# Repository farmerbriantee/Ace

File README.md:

# AgOpenGPS  ****  Ace

Ace is a new way to run AOG where the modules are small, and everything is on the udp network.

This is a development Repo and changes often. 

*** Important ****

If you distribute copies of such a program, whether
gratis or for a fee, you must pass on to the recipients the same
freedoms that you received.  You must make sure that they, too, receive
or can get the source code.  And you must show them these terms so they
know their rights as Outlined in the GPLv3 License.

THIS SOFTWARE IS PROVIDED BY THE COPYRIGHT HOLDERS AND CONTRIBUTORS "AS IS" AND ANY EXPRESS OR IMPLIED WARRANTIES, INCLUDING, BUT NOT LIMITED TO, THE IMPLIED WARRANTIES OF MERCHANTABILITY AND FITNESS FOR A PARTICULAR PURPOSE ARE DISCLAIMED.
IN NO EVENT SHALL <COPYRIGHT HOLDER> BE LIABLE FOR ANY DIRECT, INDIRECT, INCIDENTAL, SPECIAL, EXEMPLARY, OR CONSEQUENTIAL DAMAGES (INCLUDING, BUT NOT LIMITED TO, PROCUREMENT OF SUBSTITUTE GOODS OR SERVICES;
LOSS OF USE, DATA, OR PROFITS; OR BUSINESS INTERRUPTION) HOWEVER CAUSED AND ON ANY THEORY OF LIABILITY, WHETHER IN CONTRACT, STRICT LIABILITY, OR TORT (INCLUDING NEGLIGENCE OR OTHERWISE) ARISING IN ANY WAY OUT OF THE USE OF THIS SOFTWARE, EVEN IF ADVISED OF THE POSSIBILITY OF SUCH DAMAGE.

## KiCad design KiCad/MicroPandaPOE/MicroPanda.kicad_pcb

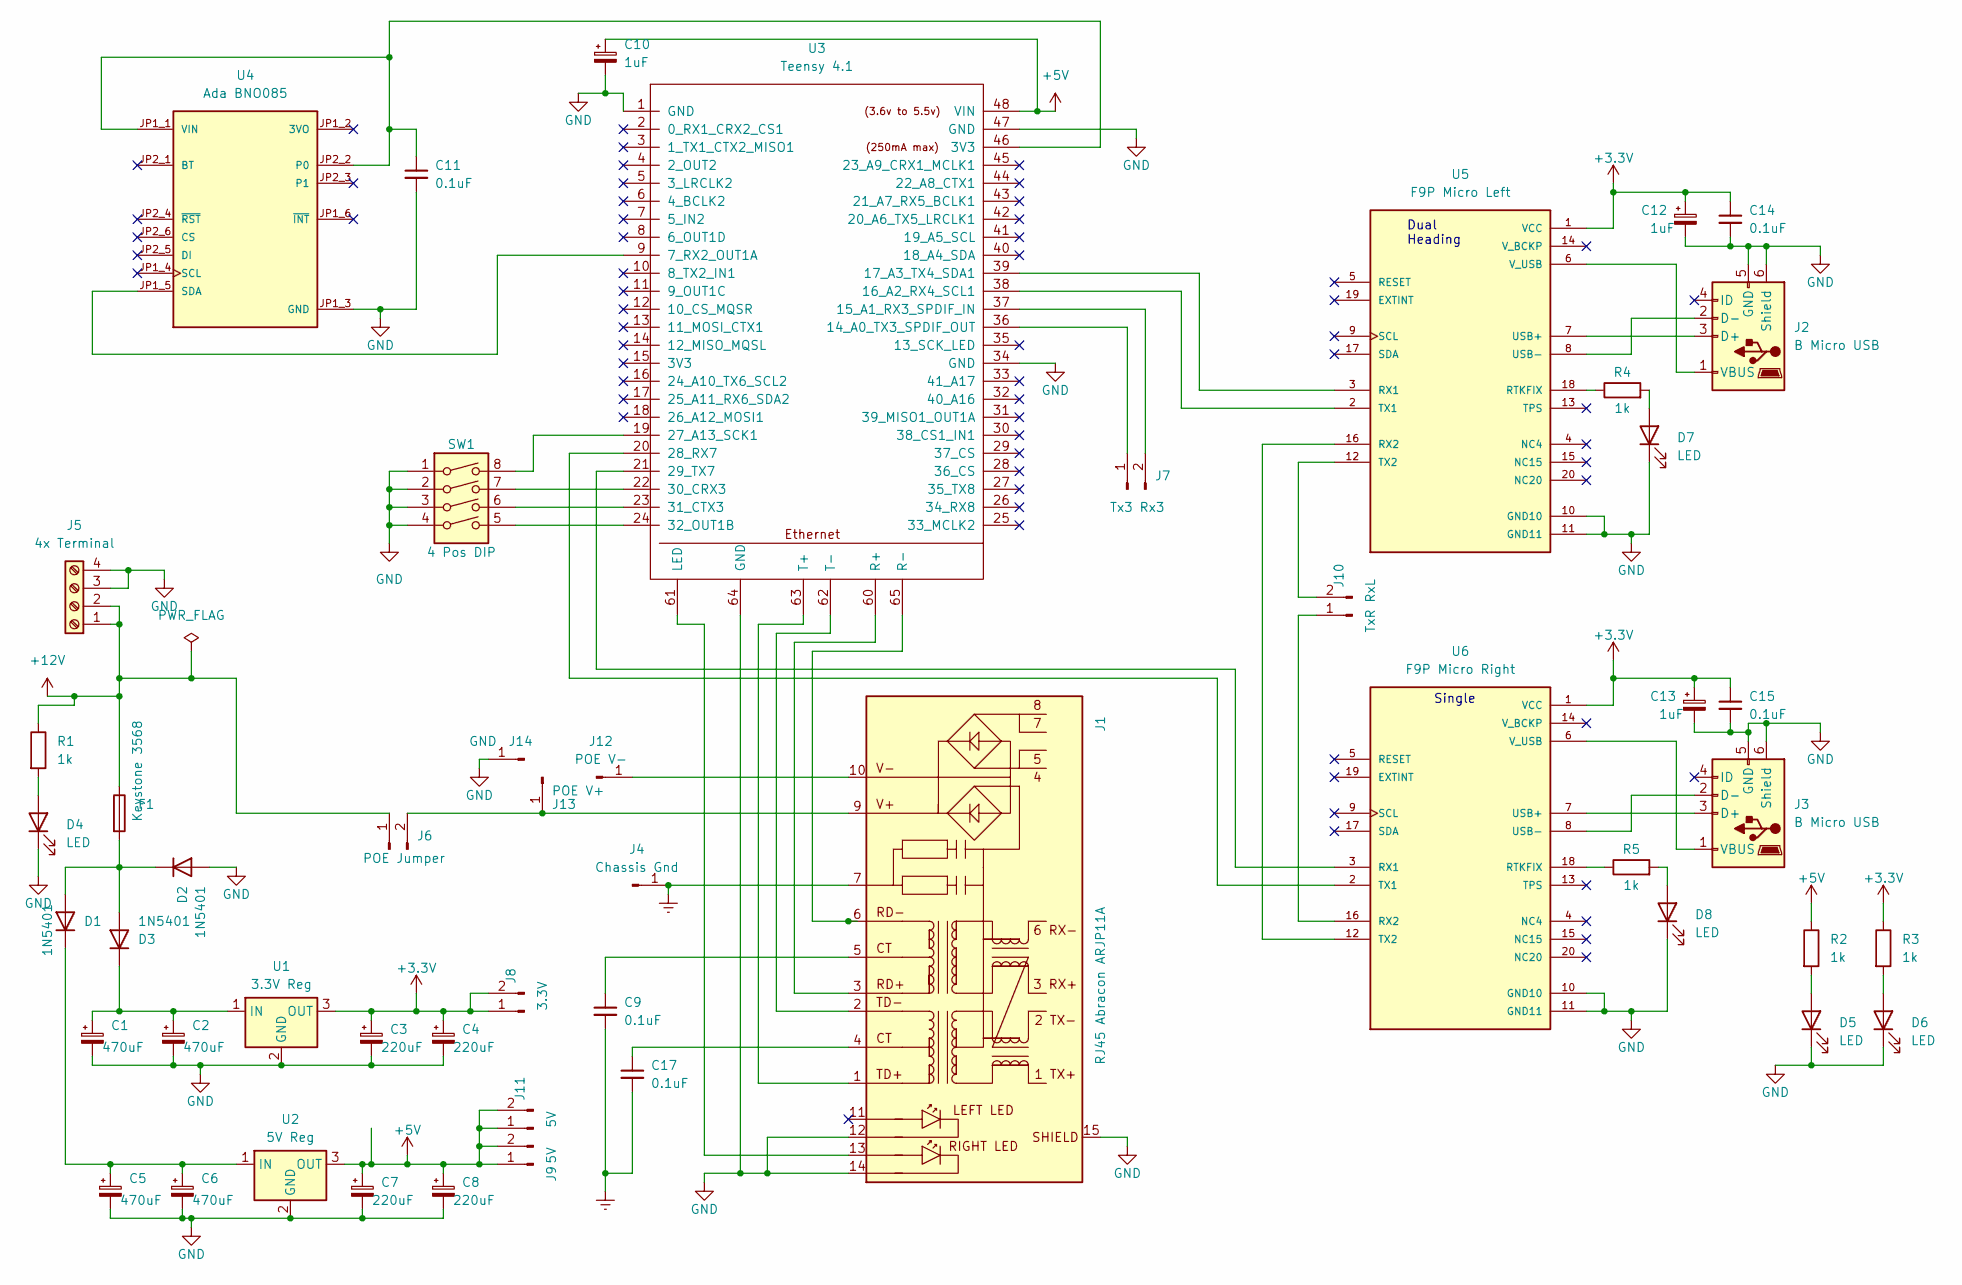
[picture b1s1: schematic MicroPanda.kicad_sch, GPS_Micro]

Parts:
C1, C2, C5, C6: 470uF; CP_Radial_D8.0mm_P5.00mm
C3, C4, C7, C8: 220uF; CP_Radial_D8.0mm_P3.50mm
C9, C11, C14, C15, C17: 0.1uF; C_Disc_D7.0mm_W2.5mm_P5.00mm
C10, C12, C13: 1uF; CP_Radial_D6.3mm_P2.50mm
D1, D2, D3: 1N5401; D_DO-201AD_P15.24mm_Horizontal
D4, D5, D6, D7, D8: LED; LED_D2.0mm_W4.0mm_H2.8mm_FlatTop
F1: Keystone 3568; Fuseholder_Blade_Mini_Keystone_3568
J1: RJ45 Abracon ARJP11A; RJ45_Abracon_ARJP11A-MA_Horizontal
J2, J3: B Micro USB; USB_Mini_B_AdamTech_musb_b5_s_vt_02_TH
J4: Chassis Gnd; Pin_D1.3mm_L11.0mm_LooseFit
J5: 4x Terminal; TerminalBlock_Phoenix_MKDS-1,5-4-5.08_1x04_P5.08mm_Horizont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
J6: POE Jumper; PinSocket_1x02_P2.54mm_Vertical
J7: Tx3 Rx3; PinSocket_1x02_P2.54mm_Vertical
J8: 3.3V; PinSocket_1x02_P2.54mm_Vertical
J9, J11: 5V; PinSocket_1x02_P2.54mm_Vertical
J10: TxR RxL; PinSocket_1x02_P2.54mm_Vertical
J12: POE V-; Pin_D1.3mm_L11.0mm_LooseFit
J13: POE V+; Pin_D1.3mm_L11.0mm_LooseFit
J14: GND; Pin_D1.3mm_L11.0mm_LooseFit
R1, R2, R3: 1k; R_Axial_DIN0207_L6.3mm_D2.5mm_P10.16mm_Horizontal
R4, R5: 1k; R_Axial_DIN0204_L3.6mm_D1.6mm_P2.54mm_Vertical
SW1: 4 Pos DIP; SW_DIP_SPSTx04_Slide_9.78x12.34mm_W7.62mm_P2.54mm
U1: 3.3V Reg; Converter_DCDC_Murata_OKI-78SR_Vertical
U2: 5V Reg; Converter_DCDC_Murata_OKI-78SR_Vertical
U3: Teensy 4.1; Teensy41_BGT
U4: Ada BNO085; BNO085_Adafruit_4754; PARTREV 2021-03-16
U5: F9P Micro Left; MODULE_AS-RTK2B-MICRO-F9P-L1L2SMATH-00; PARTREV N/A
U6: F9P Micro Right; MODULE_AS-RTK2B-MICRO-F9P-L1L2SMATH-00; PARTREV N/A

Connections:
+3.3V: C3.1, C4.1, C12.1, C13.1, C14.1, C15.1, J8.1, J8.2, R3.1, U1.3 (OUT), U5.1 (VCC), U6.1 (VCC)
+5V: C7.1, C8.1, C10.1, J9.1, J9.2, J11.1, J11.2, R2.1, U2.3 (OUT), U3.48 (VIN)
+12V: F1.1, J5.1, J5.2, J6.1, R1.1
Earth: C9.2, C17.2, J1.7, J4.1
GND: C1.2, C2.2, C3.2, C4.2, C5.2, C6.2, C7.2, C8.2, C10.2, C11.2, C12.2, C13.2, C14.2, C15.2, D2.2 (A), D4.1 (K), D5.1 (K), D6.1 (K), D7.1 (K), D8.1 (K), J1.12 (LLED-), J1.14 (RLED-), J1.15 (SHIELD), J2.5 (GND), J2.6 (Shield), J3.5 (GND), J3.6 (Shield), J5.3, J5.4, J14.1, SW1.1, SW1.2, SW1.3, SW1.4, U1.2 (GND), U2.2 (GND), U3.1 (GND), U3.34 (GND), U3.47 (GND), U3.64 (GND), U4.JP1_3 (GND), U5.10 (GND10), U5.11 (GND11), U6.10 (GND10), U6.11 (GND11)
unnamed: C1.1, C2.1, D3.1 (K), U1.1 (IN)
unnamed: C5.1, C6.1, D1.1 (K), U2.1 (IN)
unnamed: C9.1, J1.5 (CT)
unnamed: C11.1, U3.46 (3V3), U4.JP1_1 (VIN), U4.JP2_2 (P0)
unnamed: C17.1, J1.4 (CT)
unnamed: D1.2 (A), D2.1 (K), D3.2 (A), F1.2
unnamed: D4.2 (A), R1.2
unnamed: D5.2 (A), R2.2
unnamed: D6.2 (A), R3.2
unnamed: D7.2 (A), R4.2
unnamed: D8.2 (A), R5.2
unnamed: J1.1 (TD+), U3.63 (T+)
unnamed: J1.2 (TD-), U3.62 (T-)
unnamed: J1.3 (RD+), U3.60 (R+)
unnamed: J1.6 (RD-), U3.65 (R-)
unnamed: J1.9 (V+), J6.2, J13.1
unnamed: J1.10 (V-), J12.1
unnamed: J1.13 (RLED+), U3.61 (LED)
unnamed: J2.1 (VBUS), U5.6 (V_USB)
unnamed: J2.2 (D-), U5.8 (USB-)
unnamed: J2.3 (D+), U5.7 (USB+)
unnamed: J3.1 (VBUS), U6.6 (V_USB)
unnamed: J3.2 (D-), U6.8 (USB-)
unnamed: J3.3 (D+), U6.7 (USB+)
unnamed: J7.1, U3.36 (14_A0_TX3_SPDIF_OUT)
unnamed: J7.2, U3.37 (15_A1_RX3_SPDIF_IN)
unnamed: J10.1, U6.16 (RX2)
unnamed: J10.2, U5.12 (TX2)
unnamed: R4.1, U5.18 (RTKFIX)
unnamed: R5.1, U6.18 (RTKFIX)
unnamed: SW1.5, U3.24 (32_OUT1B)
unnamed: SW1.6, U3.23 (31_CTX3)
unnamed: SW1.7, U3.22 (30_CRX3)
unnamed: SW1.8, U3.19 (27_A13_SCK1)
unnamed: U3.9 (7_RX2_OUT1A), U4.JP1_5 (SDA)
unnamed: U3.20 (28_RX7), U6.2 (TX1)
unnamed: U3.21 (29_TX7), U6.3 (RX1)
unnamed: U3.38 (16_A2_RX4_SCL1), U5.2 (TX1)
unnamed: U3.39 (17_A3_TX4_SDA1), U5.3 (RX1)
unnamed: U5.16 (RX2), U6.12 (TX2)

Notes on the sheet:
Dual Heading
Single

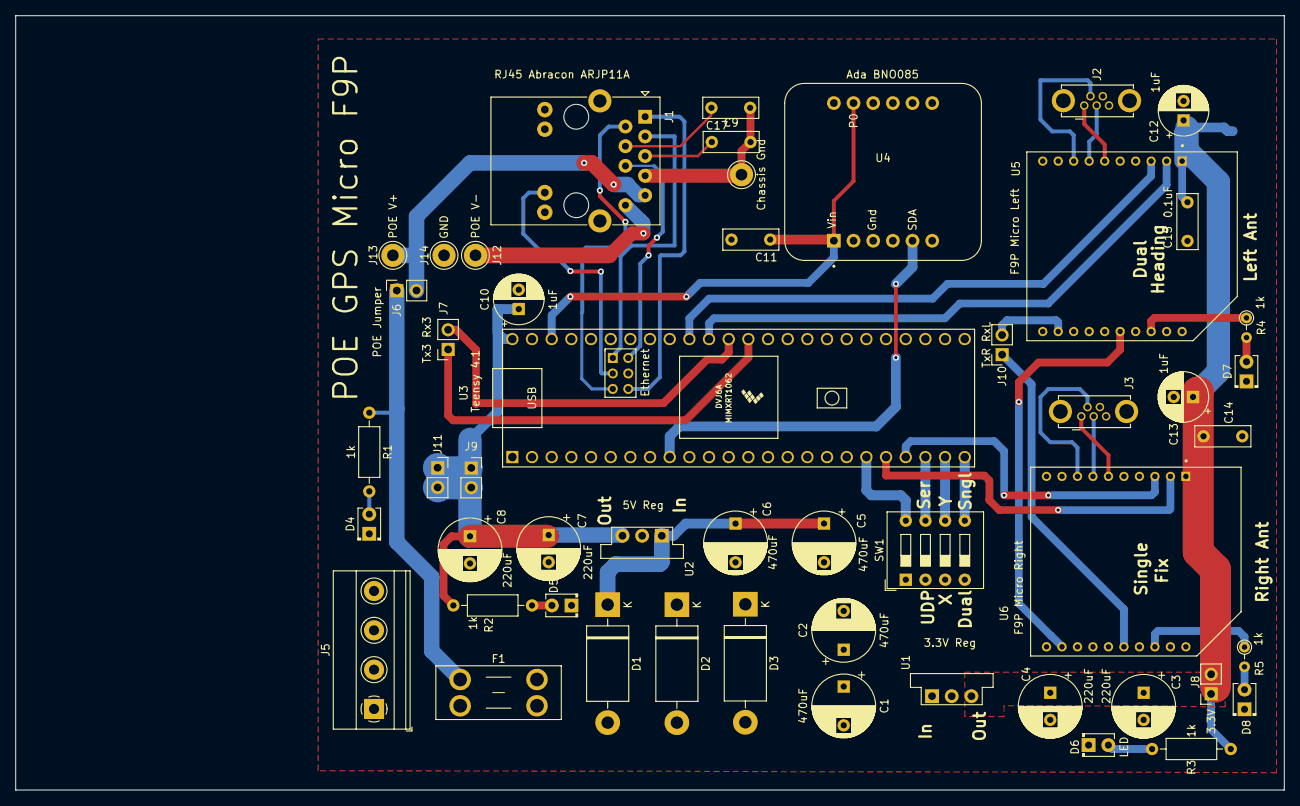
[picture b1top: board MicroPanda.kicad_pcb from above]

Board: 2 copper layers, 163.8 x 100.0 mm, 51 parts (0 on the bottom side), 45 nets.

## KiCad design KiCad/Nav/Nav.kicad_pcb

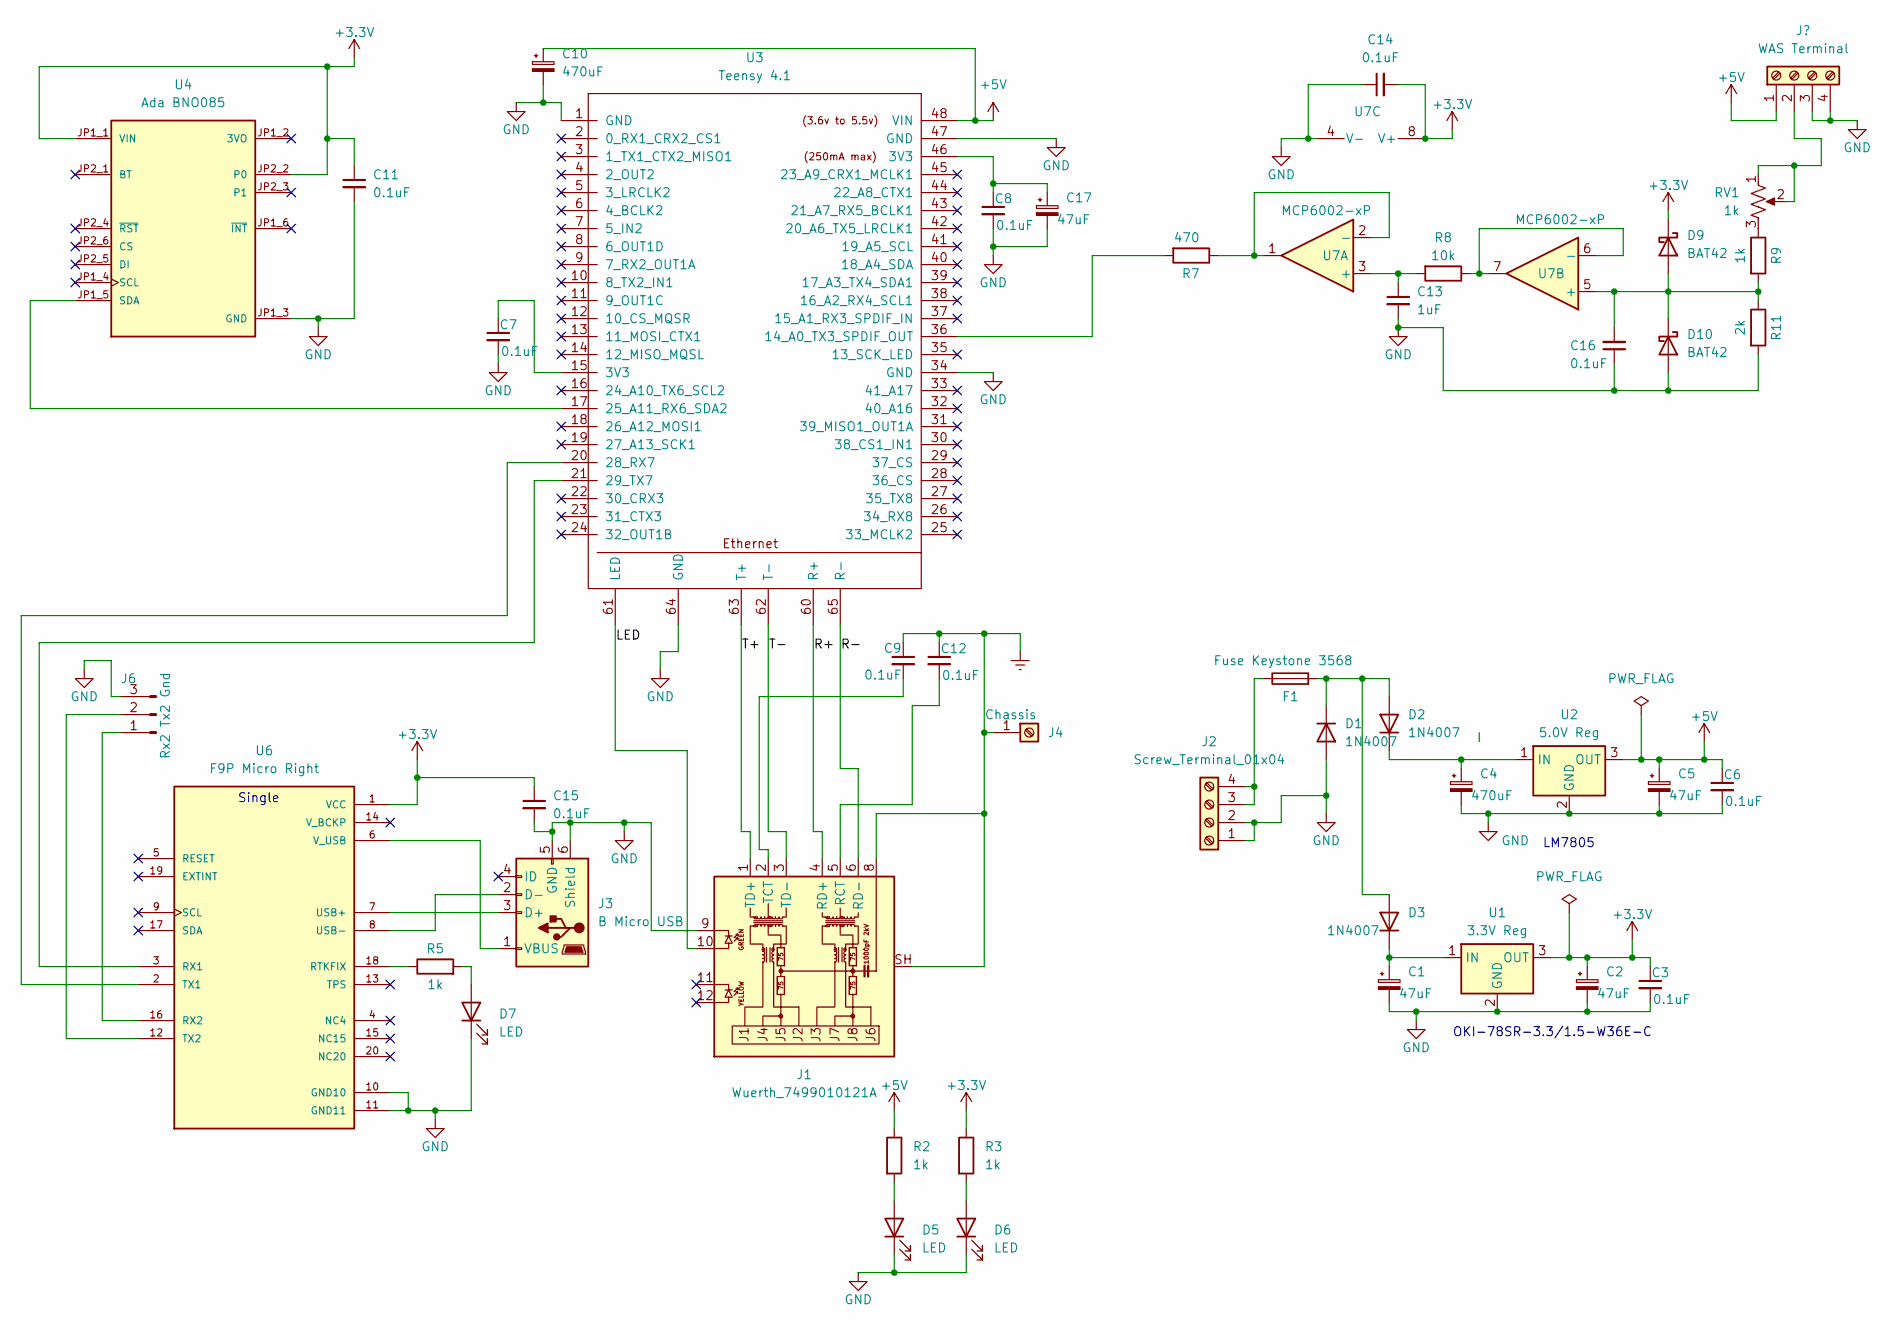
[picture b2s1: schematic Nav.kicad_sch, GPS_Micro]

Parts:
C1, C2, C5, C17: 47uF; CP_Radial_D5.0mm_P2.50mm
C3, C6, C7, C8, C9, C11, C12, C14, C15, C16: 0.1uF; C_Disc_D7.0mm_W2.5mm_P5.00mm
C4, C10: 470uF; CP_Radial_D10.0mm_P5.00mm
C13: 1uF; C_Disc_D7.0mm_W2.5mm_P5.00mm
D1, D2, D3: 1N4007; D_DO-41_SOD81_P10.16mm_Horizontal
D5, D6, D7: LED; LED_D2.0mm_W4.0mm_H2.8mm_FlatTop
D9, D10: BAT42; D_DO-35_SOD27_P7.62mm_Horizontal
F1: Fuse Keystone 3568; Fuseholder_Blade_Mini_Keystone_3568
J1: Wuerth_7499010121A; RJ45_Wuerth_7499010121A_Horizontal
J2: Screw_Terminal_01x04; TerminalBlock_TE_282834-4_1x04_P2.54mm_Horizontal
J3: B Micro USB; USB_Mini_B_AdamTech_musb_b5_s_vt_02_TH
J4: Chassis; Pin_D1.3mm_L11.3mm_W2.8mm_Flat
J6: Rx2 Tx2 Gnd; PinHeader_1x03_P2.54mm_Vertical
R2, R3, R5, R9: 1k; R_Axial_DIN0207_L6.3mm_D2.5mm_P10.16mm_Horizontal
R7: 470; R_Axial_DIN0207_L6.3mm_D2.5mm_P10.16mm_Horizontal
R8: 10k; R_Axial_DIN0207_L6.3mm_D2.5mm_P10.16mm_Horizontal
R11: 2k; R_Axial_DIN0207_L6.3mm_D2.5mm_P10.16mm_Horizontal
RV1: 1k; Potentiometer_Bourns_3296Y_Vertical
U1: 3.3V Reg; Converter_DCDC_Murata_OKI-78SR_Vertical
U2: 5.0V Reg; Converter_DCDC_Murata_OKI-78SR_Vertical
U3: Teensy 4.1; Teensy41_BGT
U4: Ada BNO085; BNO085_Adafruit_4754; PARTREV 2021-03-16
U6: F9P Micro Right; MODULE_AS-RTK2B-MICRO-F9P-L1L2SMATH-00; PARTREV N/A
U7: MCP6002-xP; DIP-8_W7.62mm

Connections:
+3.3V: C2.1, C3.1, C11.1, C14.2, C15.1, D9.1 (K), R3.1, U1.3 (OUT), U4.JP1_1 (VIN), U4.JP2_2 (P0), U6.1 (VCC), U7.8 (V+)
+5V: C5.1, C6.1, C10.1, R2.1, U2.3 (OUT), U3.48 (VIN); also elsewhere on the board
/LED: J1.10, U3.61 (LED)
/R+: J1.4 (RD+), U3.60 (R+)
/R-: J1.6 (RD-), U3.65 (R-)
/T+: J1.1 (TD+), U3.63 (T+)
/T-: J1.3 (TD-), U3.62 (T-)
Earth: C9.1, C12.1, J1.8, J1.SH, J4.1
GND: C1.2, C2.2, C3.2, C4.2, C5.2, C6.2, C7.2, C8.2, C10.2, C11.2, C13.2, C14.1, C15.2, C16.1, C17.2, D1.2 (A), D5.1 (K), D6.1 (K), D7.1 (K), D10.2 (A), J1.9, J2.1, J2.2, J3.5 (GND), J3.6 (Shield), J6.3, R11.2, U1.2 (GND), U2.2 (GND), U3.1 (GND), U3.34 (GND), U3.47 (GND), U3.64 (GND), U4.JP1_3 (GND), U6.10 (GND10), U6.11 (GND11), U7.4 (V-); also elsewhere on the board
unnamed: C1.1, D3.1 (K), U1.1 (IN)
unnamed: C4.1, D2.1 (K), U2.1 (IN)
unnamed: C7.1, U3.15 (3V3)
unnamed: C9.2, J1.2 (TCT)
unnamed: C12.2, J1.5 (RCT)
unnamed: C13.1, R8.2, U7.3 (+)
unnamed: C16.2, D9.2 (A), D10.1 (K), R9.2, R11.1, U7.5 (+)
unnamed: C8.1, C17.1, U3.46 (3V3)
unnamed: D1.1 (K), D2.2 (A), D3.2 (A), F1.2
unnamed: D5.2 (A), R2.2
unnamed: D6.2 (A), R3.2
unnamed: D7.2 (A), R5.2
unnamed: F1.1, J2.3, J2.4
unnamed: J3.1 (VBUS), U6.6 (V_USB)
unnamed: J3.2 (D-), U6.8 (USB-)
unnamed: J3.3 (D+), U6.7 (USB+)
unnamed 25: RV1.1, RV1.2; also elsewhere on the board
unnamed: J6.1, U6.16 (RX2)
unnamed: J6.2, U6.12 (TX2)
unnamed: R7.1, U7.1, U7.2 (-)
unnamed: R7.2, U3.36 (14_A0_TX3_SPDIF_OUT)
unnamed: R8.1, U7.6 (-), U7.7
unnamed: R9.1, RV1.3
unnamed: U3.17 (25_A11_RX6_SDA2), U4.JP1_5 (SDA)
unnamed: U3.20 (28_RX7), U6.2 (TX1)
unnamed: U3.21 (29_TX7), U6.3 (RX1)
unnamed: R5.1, U6.18 (RTKFIX)

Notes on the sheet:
OKI-78SR-3.3/1.5-W36E-C
LM7805
Single

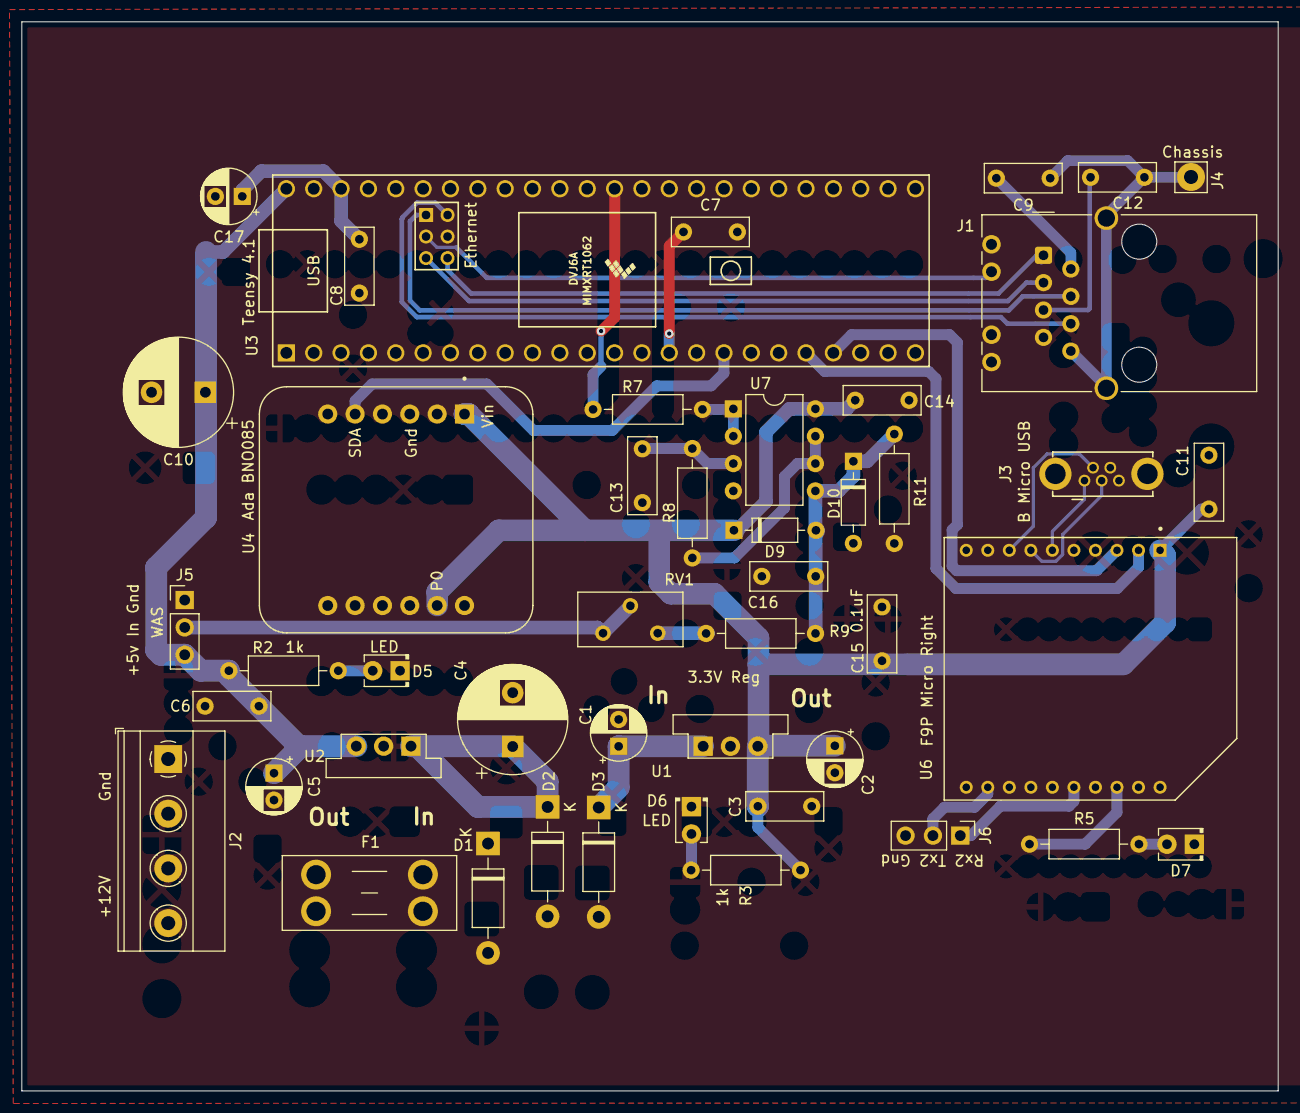
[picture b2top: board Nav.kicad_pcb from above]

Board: 2 copper layers, 116.7 x 99.3 mm, 46 parts (0 on the bottom side), 36 nets.

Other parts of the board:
J5: +5v In Gnd; PinHeader_1x03_P2.54mm_Vertical

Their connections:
+5V: J5.3; also elsewhere on the board
GND: J5.1; also elsewhere on the board
unnamed 25: J5.2; also elsewhere on the board

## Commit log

2023-02-28 initial push
2023-02-28 Fix double hardware
2023-02-28 build solutions
2023-03-01 Entered one comment lets see if this breaks github
2023-03-01 Revert "Entered one comment lets see if this breaks github"
    This reverts commit 4174c9bc2cd81f1f32c803d15affabef2187f55c.
2023-03-01 Revert "Revert "Entered one comment lets see if this breaks github""
    This reverts commit 32946e8a9a69d17417719ce24fd36d99596611ec.
2023-03-02 move pwm2 to right spot
2023-03-05 Update KiCad projects
2023-03-06 Steer Update
2023-03-08 kicad update
2023-04-18 Was going to add timing but TH 40ms was already present lets getter on the tractor.
2023-04-18 Rename teensy NAV file, nothing to do but drive it and see what happens.
2023-04-19 Revert "Rename teensy NAV file, nothing to do but drive it and see what happens."
    This reverts commit fa01579b2917f2d7c13ee7665503f6d7539c4171.
2023-10-14 AgTwo
2023-10-14 update Ace AOG to current 573
